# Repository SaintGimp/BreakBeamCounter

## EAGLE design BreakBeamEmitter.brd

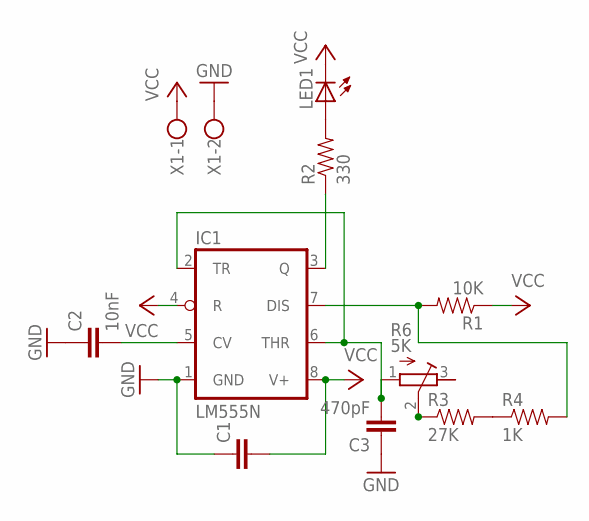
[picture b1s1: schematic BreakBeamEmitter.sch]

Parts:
C1: CAPPTH1; CAP-PTH-5MM
C2: 10nF; CAP-PTH-5MM
C3: 470pF; CAP-PTH-5MM
IC1: LM555N; DIL08-ROUND
LED1: LED5MM
R1: 10K; AXIAL-0.3
R2: 330; AXIAL-0.3
R3: 27K; AXIAL-0.3
R4: 1K; AXIAL-0.3
R6: 5K; RTRIM64Y
X1: W237-102

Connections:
GND: C1.1, C2.1, C3.1, IC1.1 (GND), X1.2
unnamed: C3.2, IC1.2 (TR), IC1.6 (THR), R6.1 (E)
unnamed: R3.P$2 (2), R4.P$1 (1)
unnamed: R3.P$1 (1), R6.2 (S)
unnamed: C2.2, IC1.5 (CV)
unnamed: LED1.A, R2.P$2 (2)
unnamed: IC1.3 (Q), R2.P$1 (1)
unnamed: IC1.7 (DIS), R1.P$2 (2), R4.P$2 (2)
VCC: C1.2, IC1.4 (R), IC1.8 (V+), LED1.K (C), R1.P$1 (1), X1.1

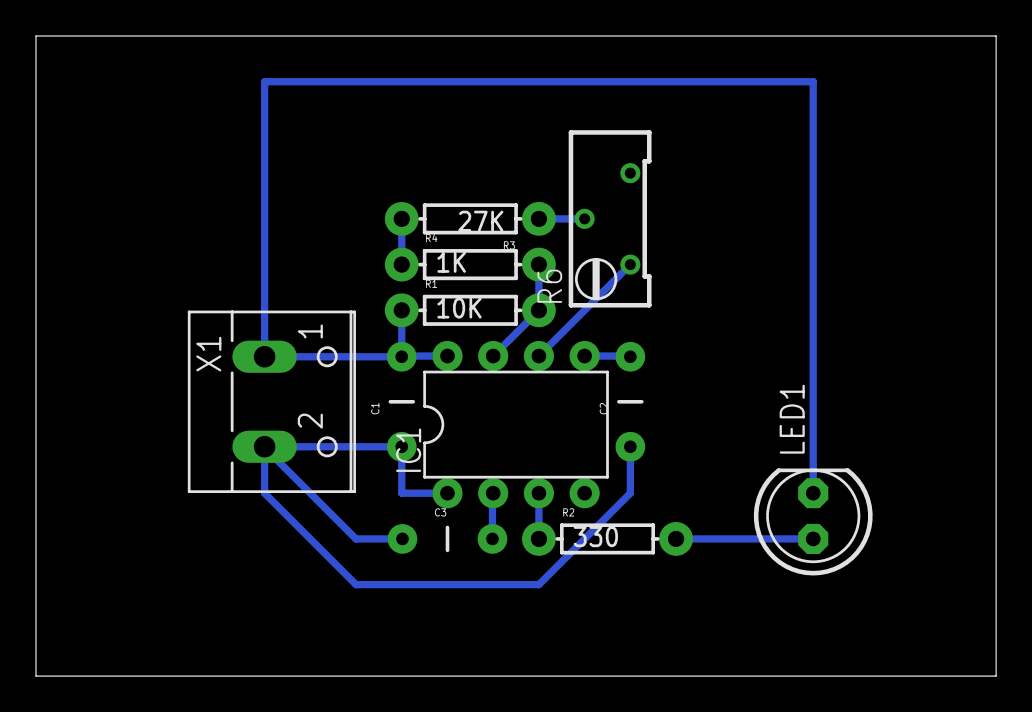
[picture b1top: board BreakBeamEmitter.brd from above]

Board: 2 copper layers, 53.3 x 35.6 mm, 11 parts (0 on the bottom side), 9 nets.

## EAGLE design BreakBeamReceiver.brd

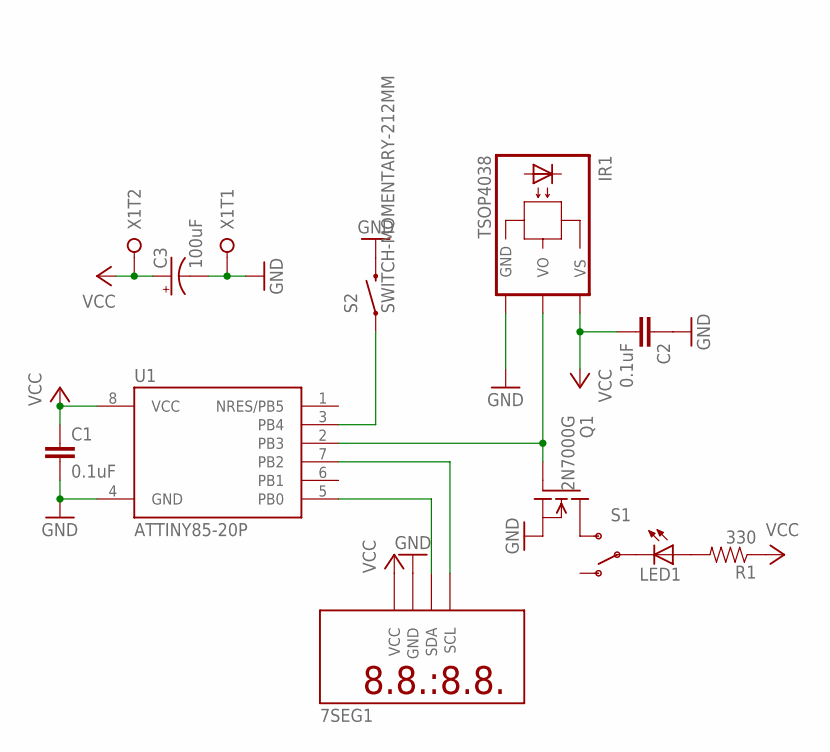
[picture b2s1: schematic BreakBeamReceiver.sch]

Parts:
7SEG1: 7-SEGMENT-BACKPACK
C1, C2: 0.1uF; CAPACITOR-5MM
C3: 100uF; CPOL-RADIAL-100UF-25V
IR1: TSOP4038; TSOP
LED1: LED5MM
Q1: 2N7000G; TO92-INLINE
R1: 330; AXIAL-5MM
S1: SWITCH-SPDTPTH; SWITCH-SPDT
S2: SWITCH-MOMENTARY-212MM; TACTILE-PTH-12MM
U1: ATTINY85-20P; PDIP08_300MIL
X1: SCREW-TERM-2

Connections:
GND: 7SEG1.GND, C1.2, C2.1, C3.2 (-), IR1.GND, Q1.1 (SRC), S2.3 (2), U1.4 (GND), X1.1
unnamed: LED1.K (C), S1.2
unnamed: LED1.A, R1.P$2 (2)
unnamed: Q1.3 (DRN), S1.3 (S)
unnamed: IR1.VO, Q1.2 (GATE), U1.2 (PB3)
unnamed: S2.1, U1.3 (PB4)
unnamed: 7SEG1.SDA, U1.5 (PB0)
unnamed: 7SEG1.SCL, U1.7 (PB2)
VCC: 7SEG1.VCC, C1.1, C2.2, C3.1 (+), IR1.VS, R1.P$1 (1), U1.8 (VCC), X1.2

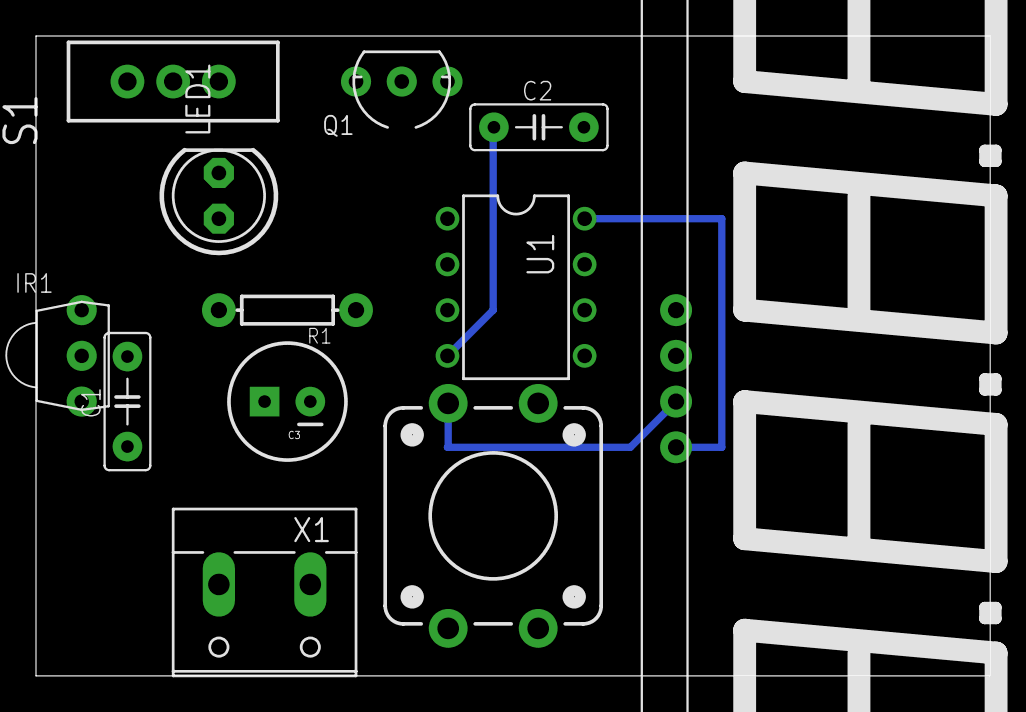
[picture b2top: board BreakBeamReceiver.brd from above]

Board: 2 copper layers, 53.0 x 35.5 mm, 12 parts (0 on the bottom side), 9 nets.

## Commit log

2014-02-08 Initial break-beam detector code
2014-02-08 Optimized filtering for people/wildlife counting
2014-02-09 Added board files and tweaked filtering
2014-02-09 Add license
2015-03-08 Better filtering

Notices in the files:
parts and their libraries:
SparkFun-Capacitors: Licensing: CC v3.0 Share-Alike You are welcome to use this library for commercial purposes.
